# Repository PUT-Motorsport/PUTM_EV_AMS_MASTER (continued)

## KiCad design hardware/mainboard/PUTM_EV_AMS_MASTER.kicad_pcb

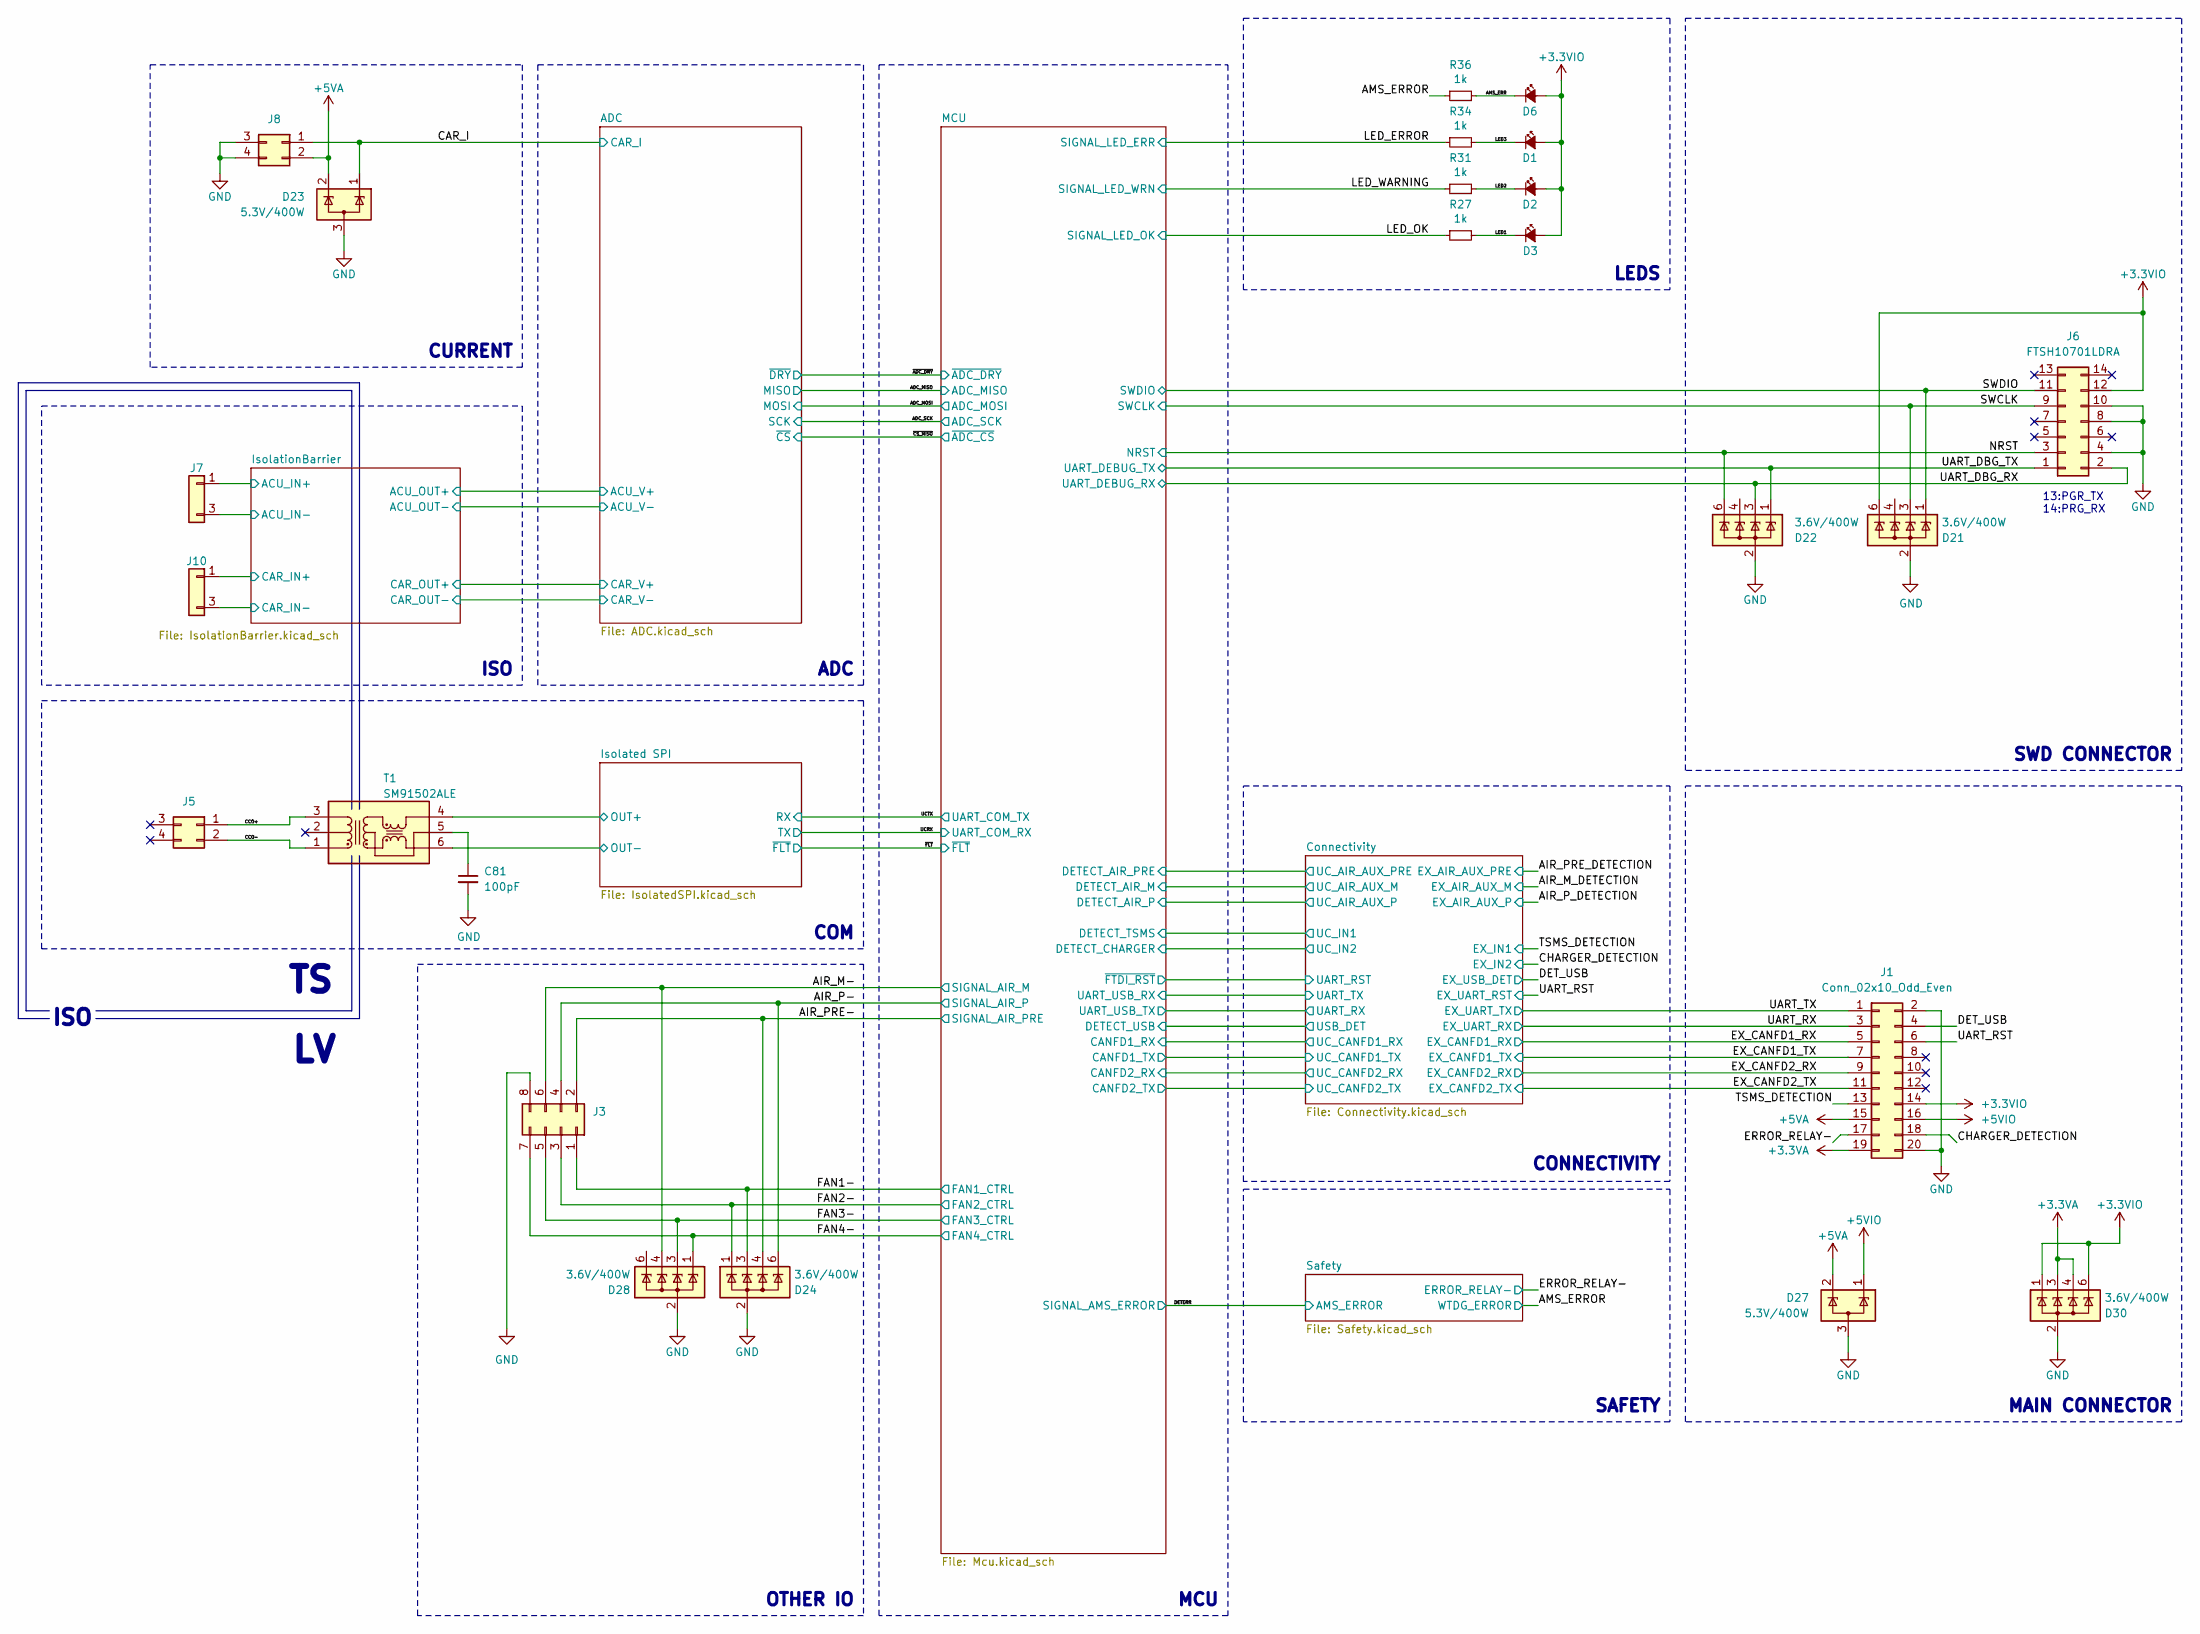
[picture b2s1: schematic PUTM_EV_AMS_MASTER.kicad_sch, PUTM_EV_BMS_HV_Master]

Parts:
C81: 100pF; C_0603_1608Metric; Manufacturer_Part_Number --; Mouser Part Number --
D1, D2, D3, D6: LED; LED_0603_1608Metric; Manufacturer_Part_Number --; Mouser Part Number --
D21, D22, D24, D28, D30: 3.6V/400W; SOT-23-6; Manufacturer_Part_Number ESDS304DBVR; Mouser Part Number 595-ESDS304DBVR
D23, D27: 5.3V/400W; SOT-23-3; Mouser Part Number 511-ESDA5V3L
J1: Conn_02x10_Odd_Even; PinHeader_2x10_P2.00mm_Vertical
J3: Conn_02x04_Odd_Even; PinHeader_2x04_P2.00mm_Vertical
J5, J8: M80-51004XX; M80-51004YY; Mouser Part Number 855-M80-5100422
J6: FTSH10701LDRA; FTSH-107-01-L-D-RA; Mouser Part Number 200-FTSH10701LDRA
J7, J10: M300-MV10345M1; M300MV10345M1; Mouser Part Number 855-M300-MV10345M1
R27, R31, R34, R36: 1k; R_0603_1608Metric; Manufacturer_Part_Number --; Mouser Part Number --
T1: SM91502ALE; SOP254P927X572-6N; Mouser Part Number 652-SM91502ALE

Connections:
+3.3VA: D30.3 (A), D30.4 (A), J1.19; also elsewhere on the board
+3.3VIO: D1.2 (A), D2.2 (A), D3.2 (A), D6.2 (A), D21.6 (A), D30.1 (A), D30.6 (A), J1.14, J6.12; also elsewhere on the board
+5VA: D23.2 (K), D27.2 (K), J1.15, J8.2; also elsewhere on the board
+5VIO: D27.1 (K), J1.16; also elsewhere on the board
/AIR_M-: D28.4 (A), J3.6; also elsewhere on the board
/AIR_P-: D24.6 (A), J3.4; also elsewhere on the board
/AIR_PRE-: D24.4 (A), J3.2; also elsewhere on the board
/AMS_ERR: D6.1 (K), R36.2
/AMS_ERROR: R36.1; also elsewhere on the board
/CAR_I: D23.1 (K), J8.1; also elsewhere on the board
/CCO+: J5.1, T1.3 (PRI_3)
/CCO-: J5.2, T1.1 (PRI_1)
/CHARGER_DETECTION: J1.18; also elsewhere on the board
/DET_USB: J1.4; also elsewhere on the board
/ERROR_RELAY-: J1.17; also elsewhere on the board
/EX_CANFD1_RX: J1.5; also elsewhere on the board
/EX_CANFD1_TX: J1.7; also elsewhere on the board
/EX_CANFD2_RX: J1.9; also elsewhere on the board
/EX_CANFD2_TX: J1.11; also elsewhere on the board
/FAN1-: D24.3 (A), J3.1; also elsewhere on the board
/FAN2-: D24.1 (A), J3.3; also elsewhere on the board
/FAN3-: D28.3 (A), J3.5; also elsewhere on the board
/FAN4-: D28.1 (A), J3.7; also elsewhere on the board
/Isolated SPI/OUT+: T1.4 (SEC_1); also elsewhere on the board
/Isolated SPI/OUT-: T1.6 (SEC_3); also elsewhere on the board
/IsolationBarrier/ACU_IN+: J7.1; also elsewhere on the board
/IsolationBarrier/ACU_IN-: J7.3; also elsewhere on the board
/IsolationBarrier/CAR_IN+: J10.1; also elsewhere on the board
/IsolationBarrier/CAR_IN-: J10.3; also elsewhere on the board
/LED1: D3.1 (K), R27.2
/LED2: D2.1 (K), R31.2
/LED3: D1.1 (K), R34.2
/LED_ERROR: R34.1; also elsewhere on the board
/LED_OK: R27.1; also elsewhere on the board
/LED_WARNING: R31.1; also elsewhere on the board
/NRST: D22.6 (A), J6.3; also elsewhere on the board
/SWCLK: D21.3 (A), J6.9; also elsewhere on the board
/SWDIO: D21.1 (A), J6.11; also elsewhere on the board
/TSMS_DETECTION: J1.13; also elsewhere on the board
/UART_DBG_RX: D22.3 (A), J6.2; also elsewhere on the board
/UART_DBG_TX: D22.1 (A), J6.1; also elsewhere on the board
/UART_RST: J1.6; also elsewhere on the board
/UART_RX: J1.3; also elsewhere on the board
/UART_TX: J1.1; also elsewhere on the board
GND: C81.2, D21.2 (K), D21.5 (NC), D22.2 (K), D22.5 (NC), D23.3 (A), D24.2 (K), D24.5 (NC), D27.3 (A), D28.2 (K), D28.5 (NC), D30.2 (K), D30.5 (NC), J1.2, J1.20, J3.8, J6.4, J6.8, J6.10, J8.3, J8.4; also elsewhere on the board
unnamed: C81.1, T1.5 (SEC_2)

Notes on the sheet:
COM
ISO
MAIN CONNECTOR
OTHER IO
MCU
LEDS
SWD CONNECTOR
13:PGR_TX 14:PRG_RX
SAFETY
CONNECTIVITY
CURRENT
ADC

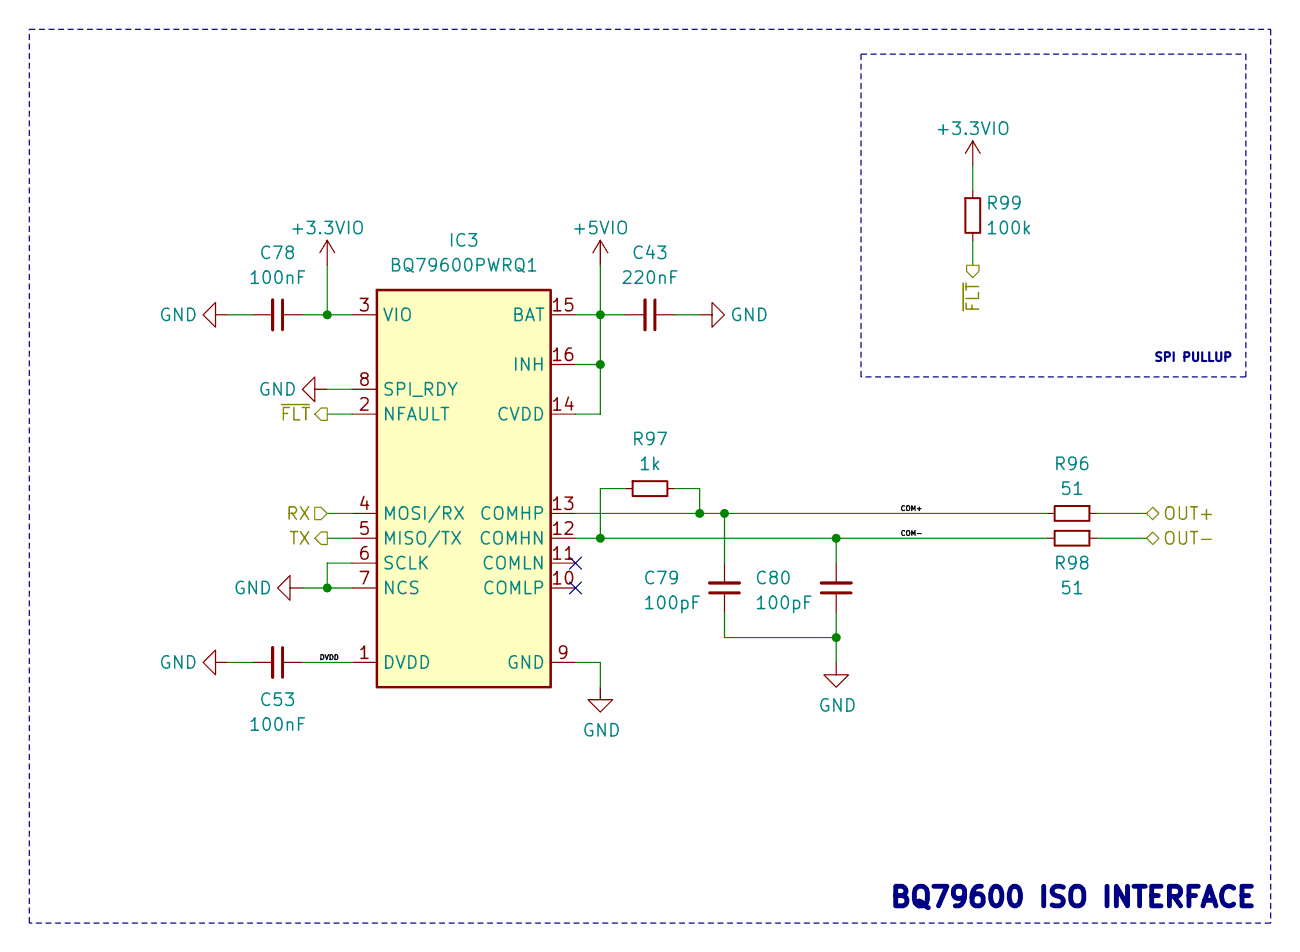
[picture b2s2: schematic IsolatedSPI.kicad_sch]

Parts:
C43: 220nF; C_0603_1608Metric; Manufacturer_Part_Number --; Mouser Part Number 963-H168SC7224KTCA1J
C53, C78: 100nF; C_0603_1608Metric; Manufacturer_Part_Number --; Mouser Part Number --
C79, C80: 100pF; C_0603_1608Metric; Manufacturer_Part_Number --; Mouser Part Number 581-06035A101K
IC3: BQ79600PWRQ1; TSSOP-16_4.4x5mm_P0.65mm; Mouser Part Number 595-BQ79600PWRQ1
R96, R98: 51; R_0603_1608Metric; Manufacturer_Part_Number --; Mouser Part Number 594-MCT06030C5109FP5
R97: 1k; R_0603_1608Metric; Manufacturer_Part_Number --; Mouser Part Number --
R99: 100k; R_0603_1608Metric; Manufacturer_Part_Number --; Mouser Part Number --

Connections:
+3.3VIO: C78.1, IC3.3 (VIO), R99.1; also elsewhere on the board
+5VIO: C43.2, IC3.14 (CVDD), IC3.15 (BAT), IC3.16 (INH); also elsewhere on the board
/Isolated SPI/COM+: C79.2, IC3.13 (COMHP), R96.2, R97.2
/Isolated SPI/COM-: C80.2, IC3.12 (COMHN), R97.1, R98.2
/Isolated SPI/DVDD: C53.1, IC3.1 (DVDD)
/Isolated SPI/OUT+: R96.1; also elsewhere on the board
/Isolated SPI/OUT-: R98.1; also elsewhere on the board
/UCRX: IC3.5 (MISO/TX); also elsewhere on the board
/UCTX: IC3.4 (MOSI/RX); also elsewhere on the board
/~FLT: IC3.2 (NFAULT), R99.2; also elsewhere on the board
GND: C43.1, C53.2, C78.2, C79.1, C80.1, IC3.6 (SCLK), IC3.7 (NCS), IC3.8 (SPI_RDY), IC3.9 (GND); also elsewhere on the board

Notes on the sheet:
SPI PULLUP
BQ79600 ISO INTERFACE

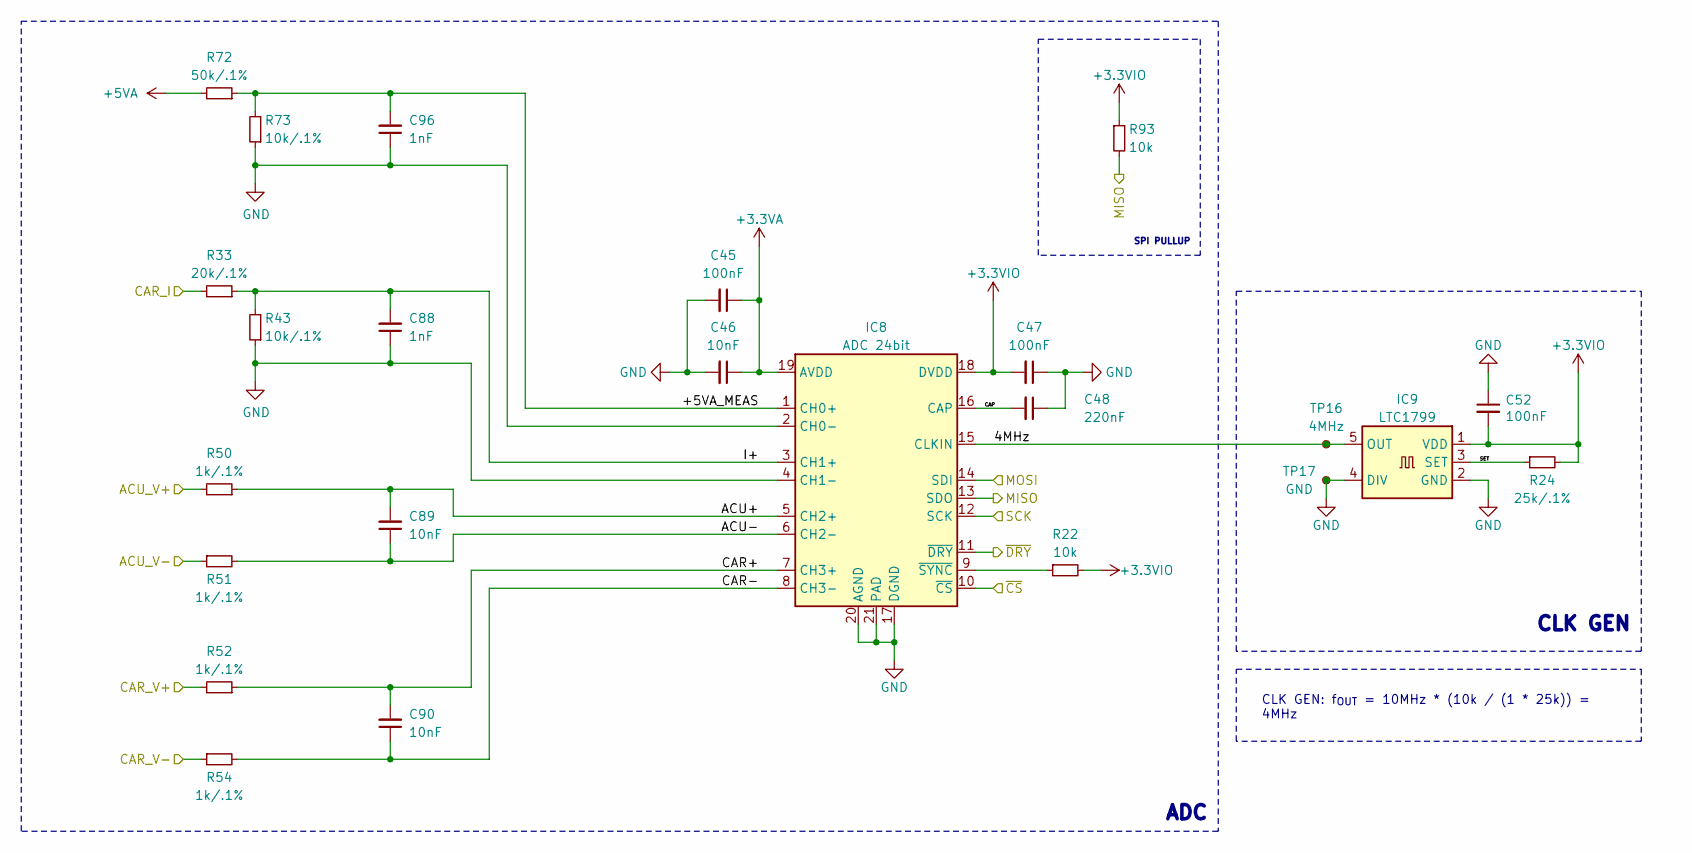
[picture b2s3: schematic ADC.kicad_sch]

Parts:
C45, C47, C52: 100nF; C_0603_1608Metric; Manufacturer_Part_Number --; Mouser Part Number --
C46, C89, C90: 10nF; C_0603_1608Metric; Manufacturer_Part_Number --; Mouser Part Number --
C48: 220nF; C_0603_1608Metric; Manufacturer_Part_Number --; Mouser Part Number 963-H168SC7224KTCA1J
C88, C96: 1nF; C_0603_1608Metric; Manufacturer_Part_Number --; Mouser Part Number --
IC8: ADC 24bit; WQFN-20-1EP_3x3mm_P0.4mm_EP1.7x1.7mm; Mouser Part Number 595-ADS131M04IRUKR
IC9: LTC1799; SOT-23-5; Mouser Part Number 584-LTC1799CS5#TRPBF
R22, R93: 10k; R_0603_1608Metric; Manufacturer_Part_Number --; Mouser Part Number --
R24: 25k/.1%; R_0603_1608Metric; Manufacturer_Part_Number --; Mouser Part Number 603-RT0603FRD078K2L
R33: 20k/.1%; R_0603_1608Metric; Manufacturer_Part_Number --; Mouser Part Number --
R43, R73: 10k/.1%; R_0603_1608Metric; Manufacturer_Part_Number --; Mouser Part Number 708-RNCF1206BKE100R
R50, R51, R52, R54: 1k/.1%; R_0603_1608Metric; Manufacturer_Part_Number --; Mouser Part Number --
R72: 50k/.1%; R_0603_1608Metric; Manufacturer_Part_Number --; Mouser Part Number 603-RT0603BRD0750KL
TP16: 4MHz; TestPoint_Pad_D1.0mm
TP17: GND; TestPoint_Pad_D1.0mm

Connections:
+3.3VA: C45.1, C46.1, IC8.19 (AVDD); also elsewhere on the board
+3.3VIO: C47.2, C52.2, IC8.18 (DVDD), IC9.1 (VDD), R22.2, R24.2, R93.1; also elsewhere on the board
+5VA: R72.2; also elsewhere on the board
/ADC/4MHz: IC8.15 (CLKIN), IC9.5 (OUT), TP16.1 (1_1)
/ADC/+5VA_MEAS: C96.2, IC8.1 (CH0+), R72.1, R73.2
/ADC/ACU+: C89.2, IC8.5 (CH2+), R50.1
/ADC/ACU-: C89.1, IC8.6 (CH2-), R51.2
/ADC/ACU_V+: R50.2; also elsewhere on the board
/ADC/ACU_V-: R51.1; also elsewhere on the board
/ADC/CAP: C48.2, IC8.16 (CAP)
/ADC/CAR+: C90.2, IC8.7 (CH3+), R52.1
/ADC/CAR-: C90.1, IC8.8 (CH3-), R54.2
/ADC/CAR_V+: R52.2; also elsewhere on the board
/ADC/CAR_V-: R54.1; also elsewhere on the board
/ADC/I+: C88.2, IC8.3 (CH1+), R33.1, R43.2
/ADC/SET: IC9.3 (SET), R24.1
/ADC_MISO: IC8.13 (SDO), R93.2; also elsewhere on the board
/ADC_MOSI: IC8.14 (SDI); also elsewhere on the board
/ADC_SCK: IC8.12 (SCK); also elsewhere on the board
/CAR_I: R33.2; also elsewhere on the board
/~ADC_DRY: IC8.11 (~DRY); also elsewhere on the board
/~CS_MISO: IC8.10 (~CS); also elsewhere on the board
GND: C45.2, C46.2, C47.1, C48.1, C52.1, C88.1, C96.1, IC8.2 (CH0-), IC8.4 (CH1-), IC8.17 (DGND), IC8.20 (AGND), IC8.21 (PAD), IC9.2 (GND), IC9.4 (DIV), R43.1, R73.1, TP17.1 (1_1); also elsewhere on the board
unnamed: IC8.9 (~SYNC), R22.1

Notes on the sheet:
SPI PULLUP
CLK GEN
ADC
CLK GEN: f_{OUT} = 10MHz * (10k / (1 * 25k)) = 4MHz

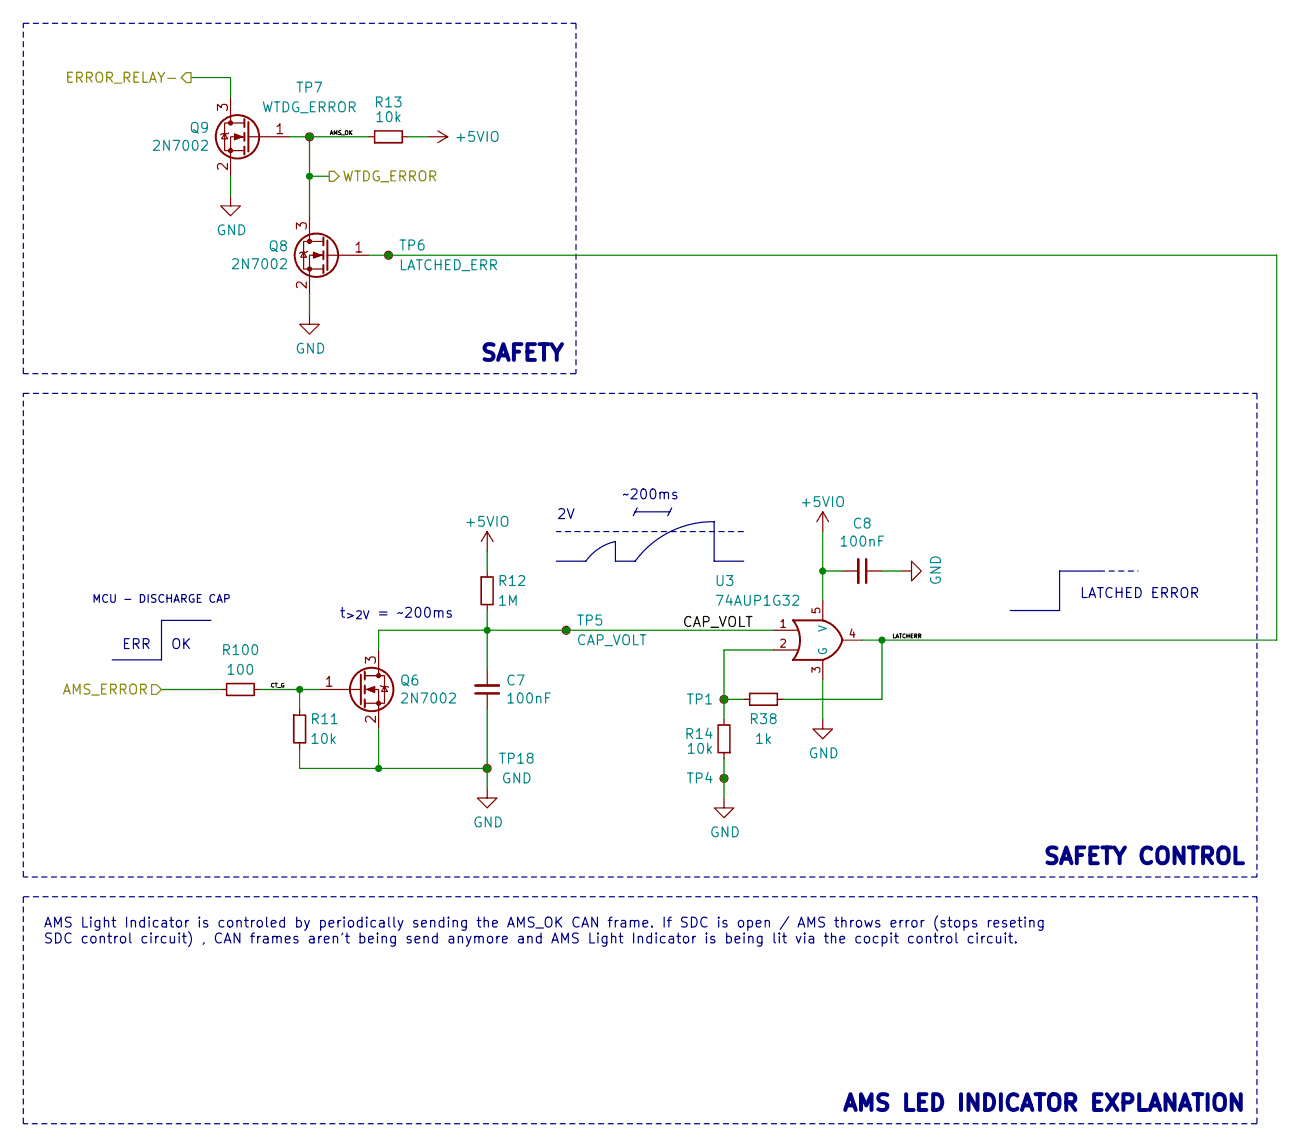
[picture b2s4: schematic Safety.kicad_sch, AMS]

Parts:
C7, C8: 100nF; C_0603_1608Metric; Manufacturer_Part_Number --; Mouser Part Number --
Q6, Q8, Q9: 2N7002; SOT-23; Manufacturer_Part_Number --; Mouser Part Number 621-DMN65D8L-7
R11, R13, R14: 10k; R_0603_1608Metric; Manufacturer_Part_Number --; Mouser Part Number --
R12: 1M; R_0603_1608Metric; Manufacturer_Part_Number --; Mouser Part Number --
R38: 1k; R_0603_1608Metric; Manufacturer_Part_Number --; Mouser Part Number --
R100: 100; R_0603_1608Metric; Manufacturer_Part_Number --; Mouser Part Number --
TP1, TP4: TestPoint_Small; TestPoint_Pad_D1.0mm
TP5: CAP_VOLT; TestPoint_Pad_D1.0mm
TP6: LATCHED_ERR; TestPoint_Pad_D1.0mm
TP7: WTDG_ERROR; TestPoint_Pad_D1.0mm
TP18: GND; TestPoint_Pad_D1.0mm
U3: 74AUP1G32; SOT-23-5; Manufacturer_Part_Number SN74AUP1G32DBVR; Mouser Part Number 595-SN74AUP1G32DBVR

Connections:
+5VIO: C8.2, R12.1, R13.2, U3.5 (V); also elsewhere on the board
/AMS_ERROR: Q8.3 (D), Q9.1 (G), R13.1, TP7.1 (1_1); also elsewhere on the board
/DETERR: R100.1; also elsewhere on the board
/ERROR_RELAY-: Q9.3 (D); also elsewhere on the board
/Safety/CAP_VOLT: C7.2, Q6.3 (D), R12.2, TP5.1 (1_1), U3.1
/Safety/CT_G: Q6.1 (G), R11.1, R100.2
/Safety/LATCHERR: Q8.1 (G), R38.1, TP6.1 (1_1), U3.4
GND: C7.1, C8.1, Q6.2 (S), Q8.2 (S), Q9.2 (S), R11.2, R14.1, TP4.1 (1_1), TP18.1 (1_1), U3.3 (G); also elsewhere on the board
unnamed: R14.2, R38.2, TP1.1 (1_1), U3.2

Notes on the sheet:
MCU - DISCHARGE CAP
AMS Light Indicator is controled by periodically sending the AMS_OK CAN frame. If SDC is open / AMS throws error (stops reseting SDC control circuit) , CAN frames aren't being send anymore and AMS Light Indicator is being lit via the cocpit control circuit.
SAFETY CONTROL
~200ms
SAFETY
AMS LED INDICATOR EXPLANATION
ERR
LATCHED ERROR
t_{>2V} = ~200ms

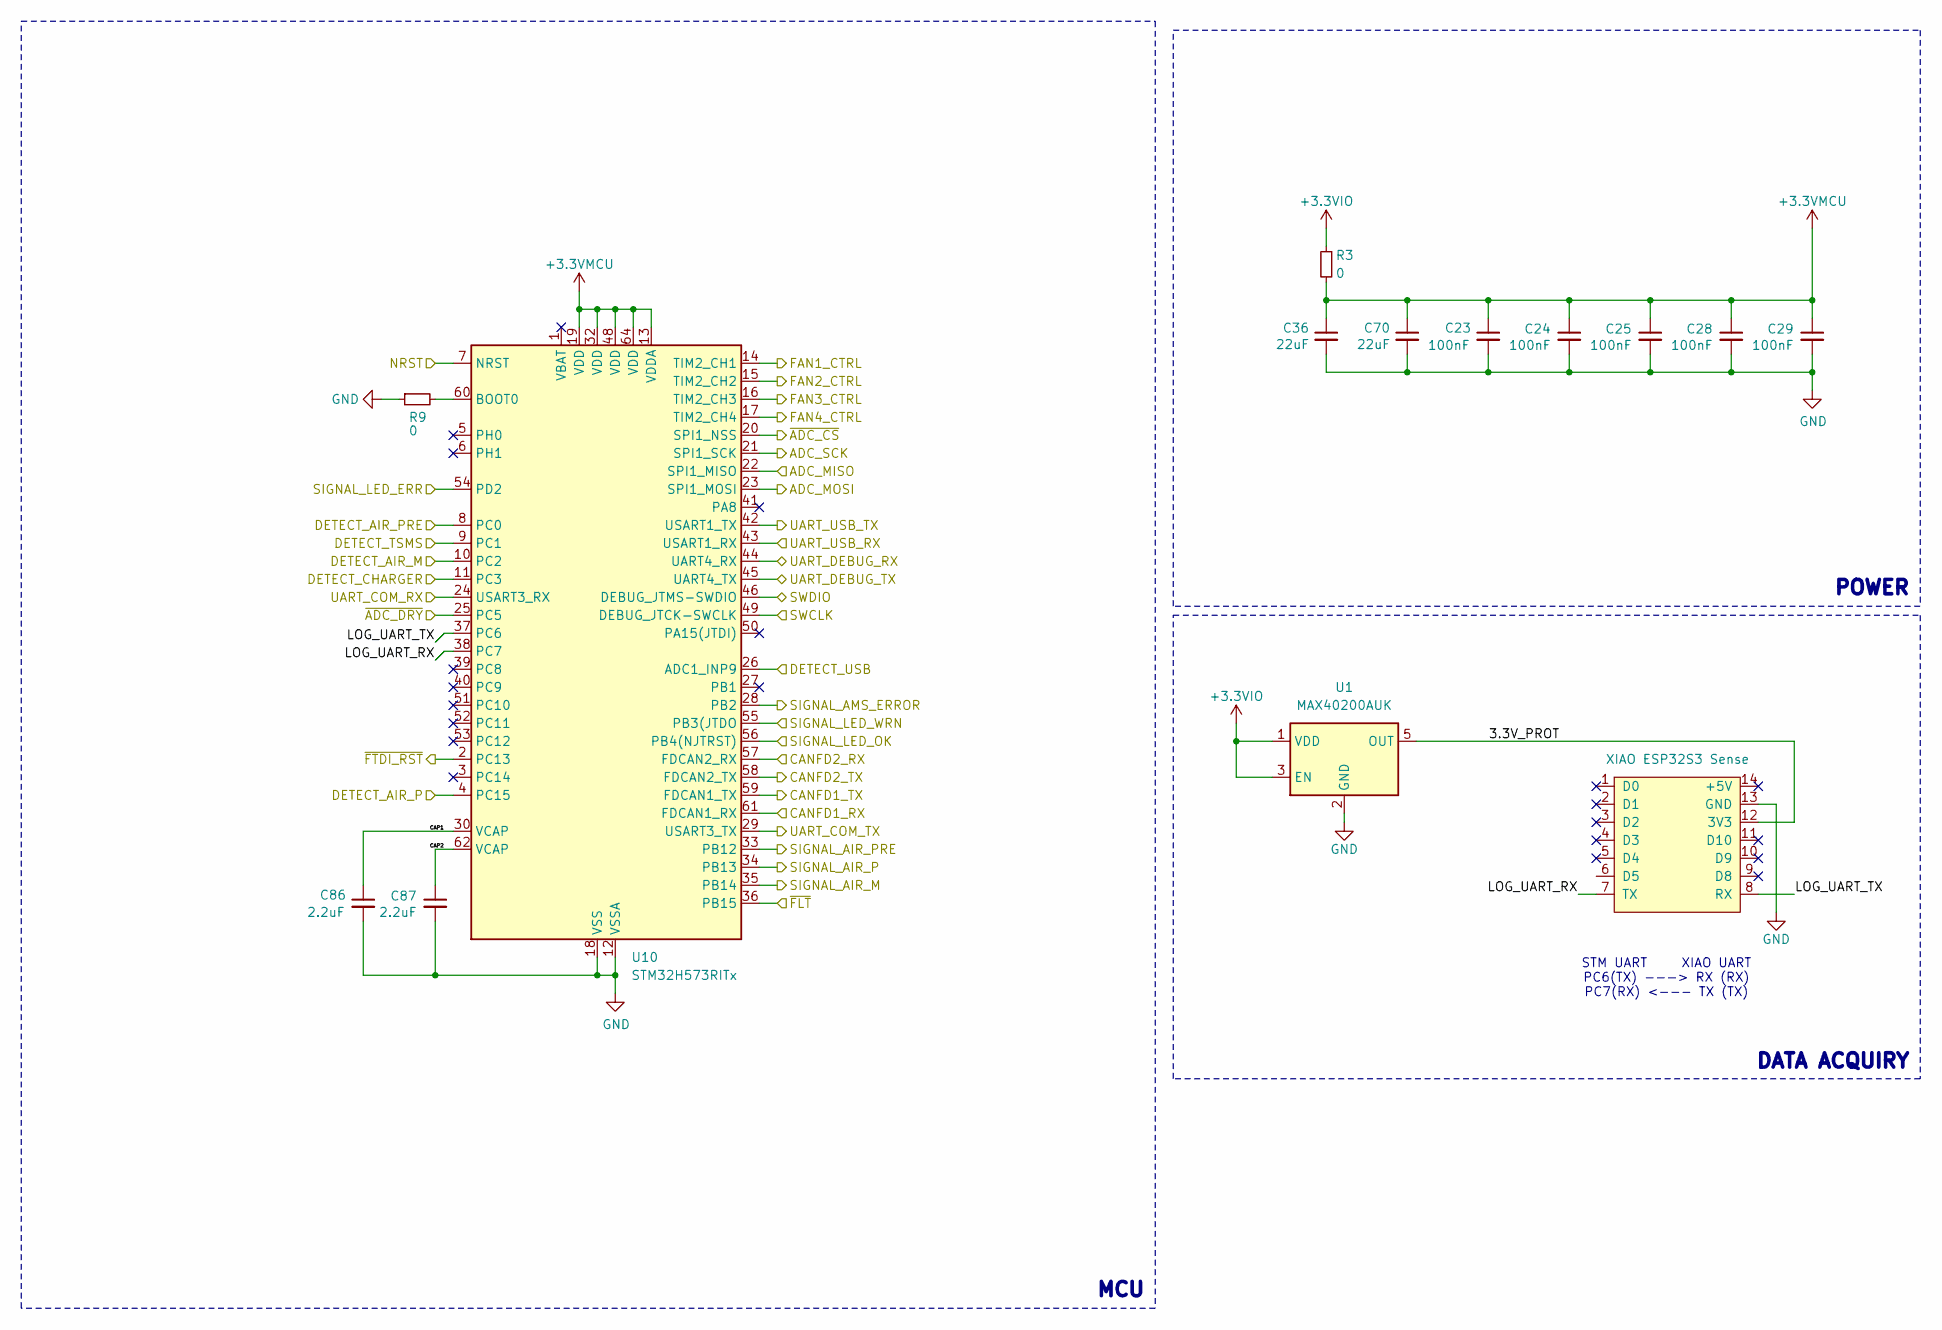
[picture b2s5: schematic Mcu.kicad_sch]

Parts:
C23, C24, C25, C28, C29: 100nF; C_0603_1608Metric; Manufacturer_Part_Number --; Mouser Part Number --
C36, C70: 22uF; C_0805_2012Metric; Manufacturer_Part_Number --; Mouser Part Number 810-C2012X5R1V226MAC
C86, C87: 2.2uF; C_0603_1608Metric; Manufacturer_Part_Number --; Mouser Part Number 603-CC603KPX7R9BB222
J2: XIAO ESP32S3 Sense; XIAO-ESP32-S3-DIP
R3, R9: 0; R_0603_1608Metric; Manufacturer_Part_Number --; Mouser Part Number --
U1: MAX40200AUK; SOT-23-5_HandSoldering; Mouser Part Number 700-MAX40200AUK+T
U10: STM32H573RITx; LQFP-64_10x10mm_P0.5mm; Mouser Part Number 511-STM32H573RIT6

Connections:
+3.3VIO: R3.1, U1.1 (VDD), U1.3 (EN); also elsewhere on the board
+3.3VMCU: C23.1, C24.1, C25.1, C28.1, C29.1, C36.1, C70.1, R3.2, U10.13 (VDDA), U10.19 (VDD), U10.32 (VDD), U10.48 (VDD), U10.64 (VDD)
/ADC_MISO: U10.22 (SPI1_MISO); also elsewhere on the board
/ADC_MOSI: U10.23 (SPI1_MOSI); also elsewhere on the board
/ADC_SCK: U10.21 (SPI1_SCK); also elsewhere on the board
/AIR_M-: U10.35 (PB14); also elsewhere on the board
/AIR_P-: U10.34 (PB13); also elsewhere on the board
/AIR_PRE-: U10.33 (PB12); also elsewhere on the board
/CHARGER_DETECTION: U10.11 (PC3); also elsewhere on the board
/DETERR: U10.28 (PB2); also elsewhere on the board
/DET_USB: U10.26 (ADC1_INP9); also elsewhere on the board
/EX_CANFD1_RX: U10.61 (FDCAN1_RX); also elsewhere on the board
/EX_CANFD1_TX: U10.59 (FDCAN1_TX); also elsewhere on the board
/EX_CANFD2_RX: U10.57 (FDCAN2_RX); also elsewhere on the board
/EX_CANFD2_TX: U10.58 (FDCAN2_TX); also elsewhere on the board
/FAN1-: U10.14 (TIM2_CH1); also elsewhere on the board
/FAN2-: U10.15 (TIM2_CH2); also elsewhere on the board
/FAN3-: U10.16 (TIM2_CH3); also elsewhere on the board
/FAN4-: U10.17 (TIM2_CH4); also elsewhere on the board
/LED_ERROR: U10.54 (PD2); also elsewhere on the board
/LED_OK: U10.56 (PB4(NJTRST)); also elsewhere on the board
/LED_WARNING: U10.55 (PB3(JTDO); also elsewhere on the board
/MCU/3.3V_PROT: J2.12 (3V3), U1.5 (OUT)
/MCU/CAP1: C86.1, U10.30 (VCAP)
/MCU/CAP2: C87.1, U10.62 (VCAP)
/MCU/DETECT_AIR_M: U10.10 (PC2)
/MCU/DETECT_AIR_P: U10.4 (PC15)
/MCU/DETECT_AIR_PRE: U10.8 (PC0)
/MCU/LOG_UART_RX: J2.7 (TX), U10.38 (PC7)
/MCU/LOG_UART_TX: J2.8 (RX), U10.37 (PC6)
/NRST: U10.7 (NRST); also elsewhere on the board
/SWCLK: U10.49 (DEBUG_JTCK-SWCLK); also elsewhere on the board
/SWDIO: U10.46 (DEBUG_JTMS-SWDIO); also elsewhere on the board
/TSMS_DETECTION: U10.9 (PC1); also elsewhere on the board
/UART_DBG_RX: U10.44 (UART4_RX); also elsewhere on the board
/UART_DBG_TX: U10.45 (UART4_TX); also elsewhere on the board
/UART_RST: U10.2 (PC13); also elsewhere on the board
/UART_RX: U10.42 (USART1_TX); also elsewhere on the board
/UART_TX: U10.43 (USART1_RX); also elsewhere on the board
/UCRX: U10.24 (USART3_RX); also elsewhere on the board
/UCTX: U10.29 (USART3_TX); also elsewhere on the board
/~ADC_DRY: U10.25 (PC5); also elsewhere on the board
/~CS_MISO: U10.20 (SPI1_NSS); also elsewhere on the board
/~FLT: U10.36 (PB15); also elsewhere on the board
GND: C23.2, C24.2, C25.2, C28.2, C29.2, C36.2, C70.2, C86.2, C87.2, J2.13 (GND), R9.1, U1.2 (GND), U10.12 (VSSA), U10.18 (VSS), U10.31 (VSS), U10.47 (VSS), U10.63 (VSS); also elsewhere on the board
unnamed: R9.2, U10.60 (BOOT0)

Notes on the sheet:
MCU
DATA ACQUIRY
STM UART XIAO UART PC6(TX) ---> RX (RX) PC7(RX) <--- TX (TX)
POWER

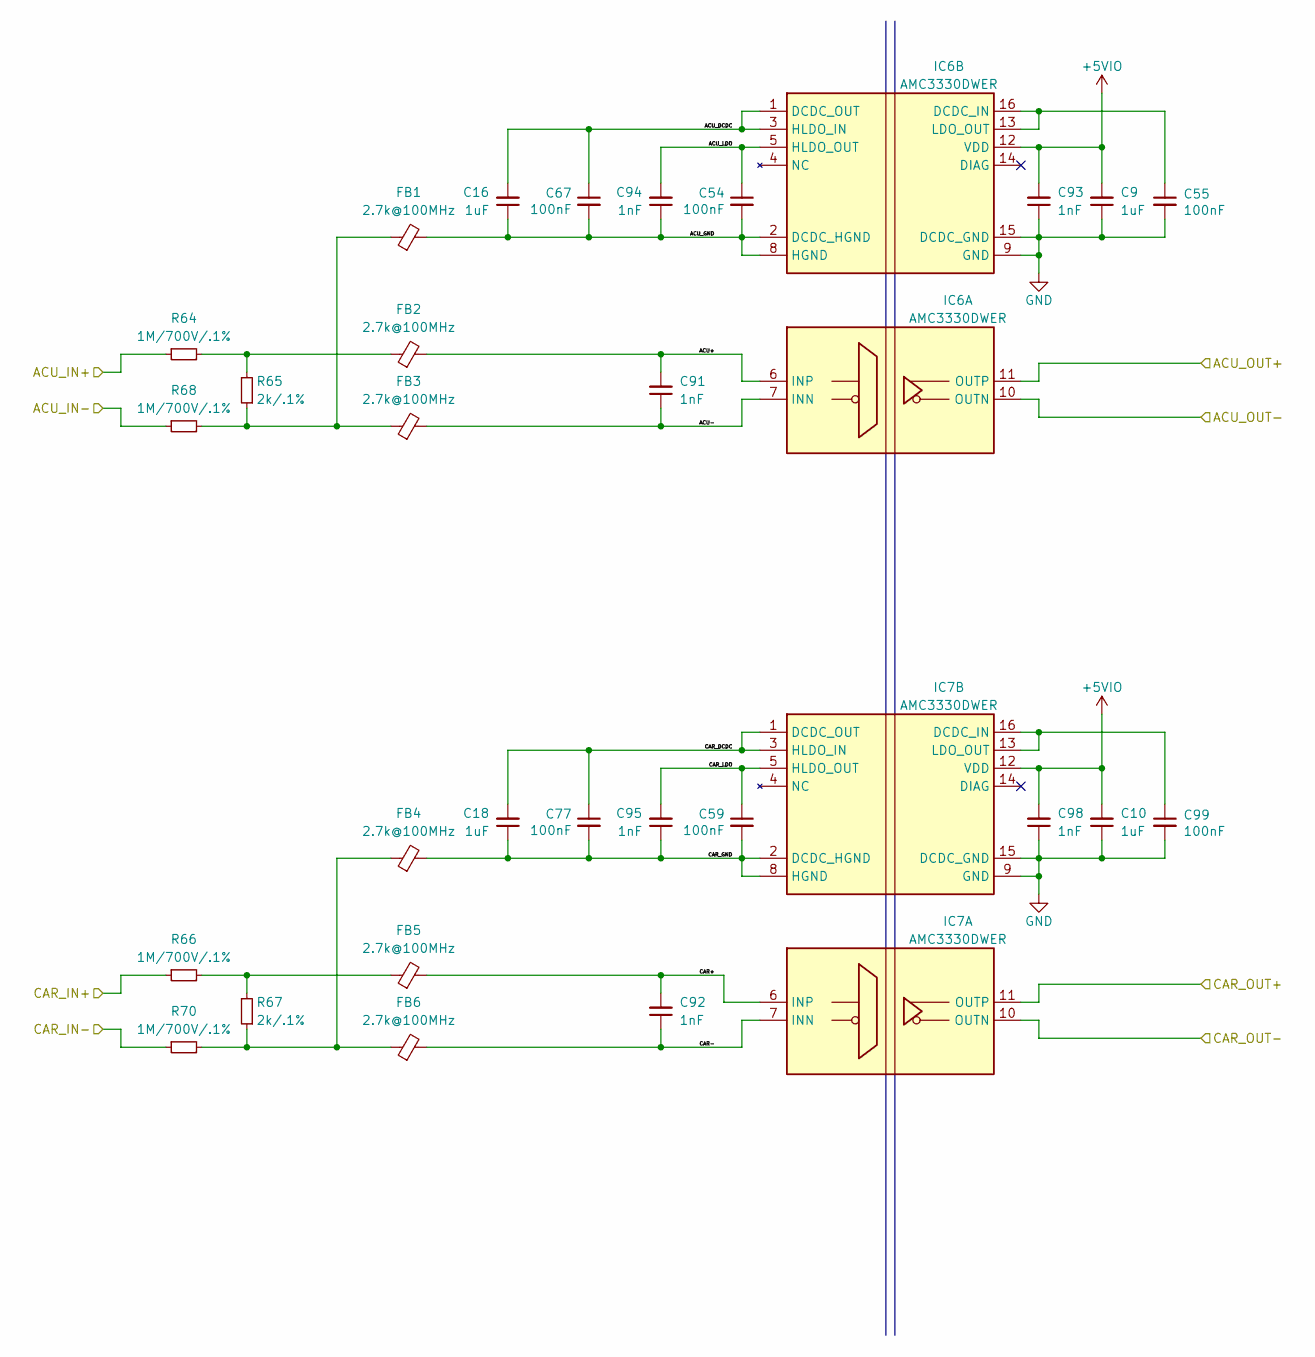
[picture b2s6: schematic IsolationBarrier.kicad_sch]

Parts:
C9, C10, C16, C18: 1uF; C_0603_1608Metric; Manufacturer_Part_Number C0603C104J3RACTU; Mouser Part Number 80-C0603C104J3R
C54, C55, C59, C67, C77, C99: 100nF; C_0603_1608Metric; Manufacturer_Part_Number --; Mouser Part Number --
C91, C92, C93, C94, C95, C98: 1nF; C_0603_1608Metric; Manufacturer_Part_Number --; Mouser Part Number --
FB1, FB2, FB3, FB4, FB5, FB6: 2.7k@100MHz; L_0805_2012Metric; Mouser Part Number 81-BLM21BD272SN1L
IC6, IC7: AMC3330DWER; SOIC-16W_7.5x10.3mm_P1.27mm; Mouser Part Number 595-AMC3330DWER
R64, R66, R68, R70: 1M/700V/.1%; R_1206_3216Metric; Manufacturer_Part_Number 754-RGV3216P-1004BT1; Mouser Part Number 754-RGV3216P-1004BT1
R65, R67: 2k/.1%; R_1206_3216Metric; Manufacturer_Part_Number --; Mouser Part Number 279-RQ73C2B4K02BTD

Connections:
+5VIO: C9.2, C10.2, C93.2, C98.2, IC6.12 (VDD), IC7.12 (VDD); also elsewhere on the board
/ADC/ACU_V+: IC6.11 (OUTP); also elsewhere on the board
/ADC/ACU_V-: IC6.10 (OUTN); also elsewhere on the board
/ADC/CAR_V+: IC7.11 (OUTP); also elsewhere on the board
/ADC/CAR_V-: IC7.10 (OUTN); also elsewhere on the board
/IsolationBarrier/ACU+: C91.2, FB2.2, IC6.6 (INP)
/IsolationBarrier/ACU-: C91.1, FB3.2, IC6.7 (INN)
/IsolationBarrier/ACU_DCDC: C16.2, C67.1, IC6.1 (DCDC_OUT), IC6.3 (HLDO_IN)
/IsolationBarrier/ACU_GND: C16.1, C54.2, C67.2, C94.1, FB1.2, IC6.2 (DCDC_HGND), IC6.8 (HGND)
/IsolationBarrier/ACU_IN+: R64.1; also elsewhere on the board
/IsolationBarrier/ACU_IN-: R68.1; also elsewhere on the board
/IsolationBarrier/ACU_LDO: C54.1, C94.2, IC6.5 (HLDO_OUT)
/IsolationBarrier/CAR+: C92.2, FB5.2, IC7.6 (INP)
/IsolationBarrier/CAR-: C92.1, FB6.2, IC7.7 (INN)
/IsolationBarrier/CAR_DCDC: C18.2, C77.1, IC7.1 (DCDC_OUT), IC7.3 (HLDO_IN)
/IsolationBarrier/CAR_GND: C18.1, C59.2, C77.2, C95.1, FB4.2, IC7.2 (DCDC_HGND), IC7.8 (HGND)
/IsolationBarrier/CAR_IN+: R66.1; also elsewhere on the board
/IsolationBarrier/CAR_IN-: R70.1; also elsewhere on the board
/IsolationBarrier/CAR_LDO: C59.1, C95.2, IC7.5 (HLDO_OUT)
GND: C9.1, C10.1, C55.2, C93.1, C98.1, C99.2, IC6.9 (GND), IC6.15 (DCDC_GND), IC7.9 (GND), IC7.15 (DCDC_GND); also elsewhere on the board
unnamed: FB1.1, FB3.1, R65.1, R68.2
unnamed: FB2.1, R64.2, R65.2
unnamed: FB4.1, FB6.1, R67.1, R70.2
unnamed: FB5.1, R66.2, R67.2
unnamed: C55.1, IC6.13 (LDO_OUT), IC6.16 (DCDC_IN)
unnamed: C99.1, IC7.13 (LDO_OUT), IC7.16 (DCDC_IN)
